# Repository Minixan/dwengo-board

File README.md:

After nearly a year of development, lots of new features and thousands of other improvements, Django 1.1 is here and ready for prime time!

For a full rundown of what's new and what's changed, consult the release notes; to grab a copy, swing by the Django download page. And for the security-conscious, signed checksums for the release tarball are available.

This release also contains the security update rolled out earlier tonight for older release series.

Django 1.1 is the result of hard work by hundreds of people who've contributed code to Django and many more who've donated their time to reporting, triaging, tracking down and helping to fix bugs and develop new features. Django literally would not be able to happen without all of you, so stop and give yourselves (and any other contributors you know) a pat on the back.

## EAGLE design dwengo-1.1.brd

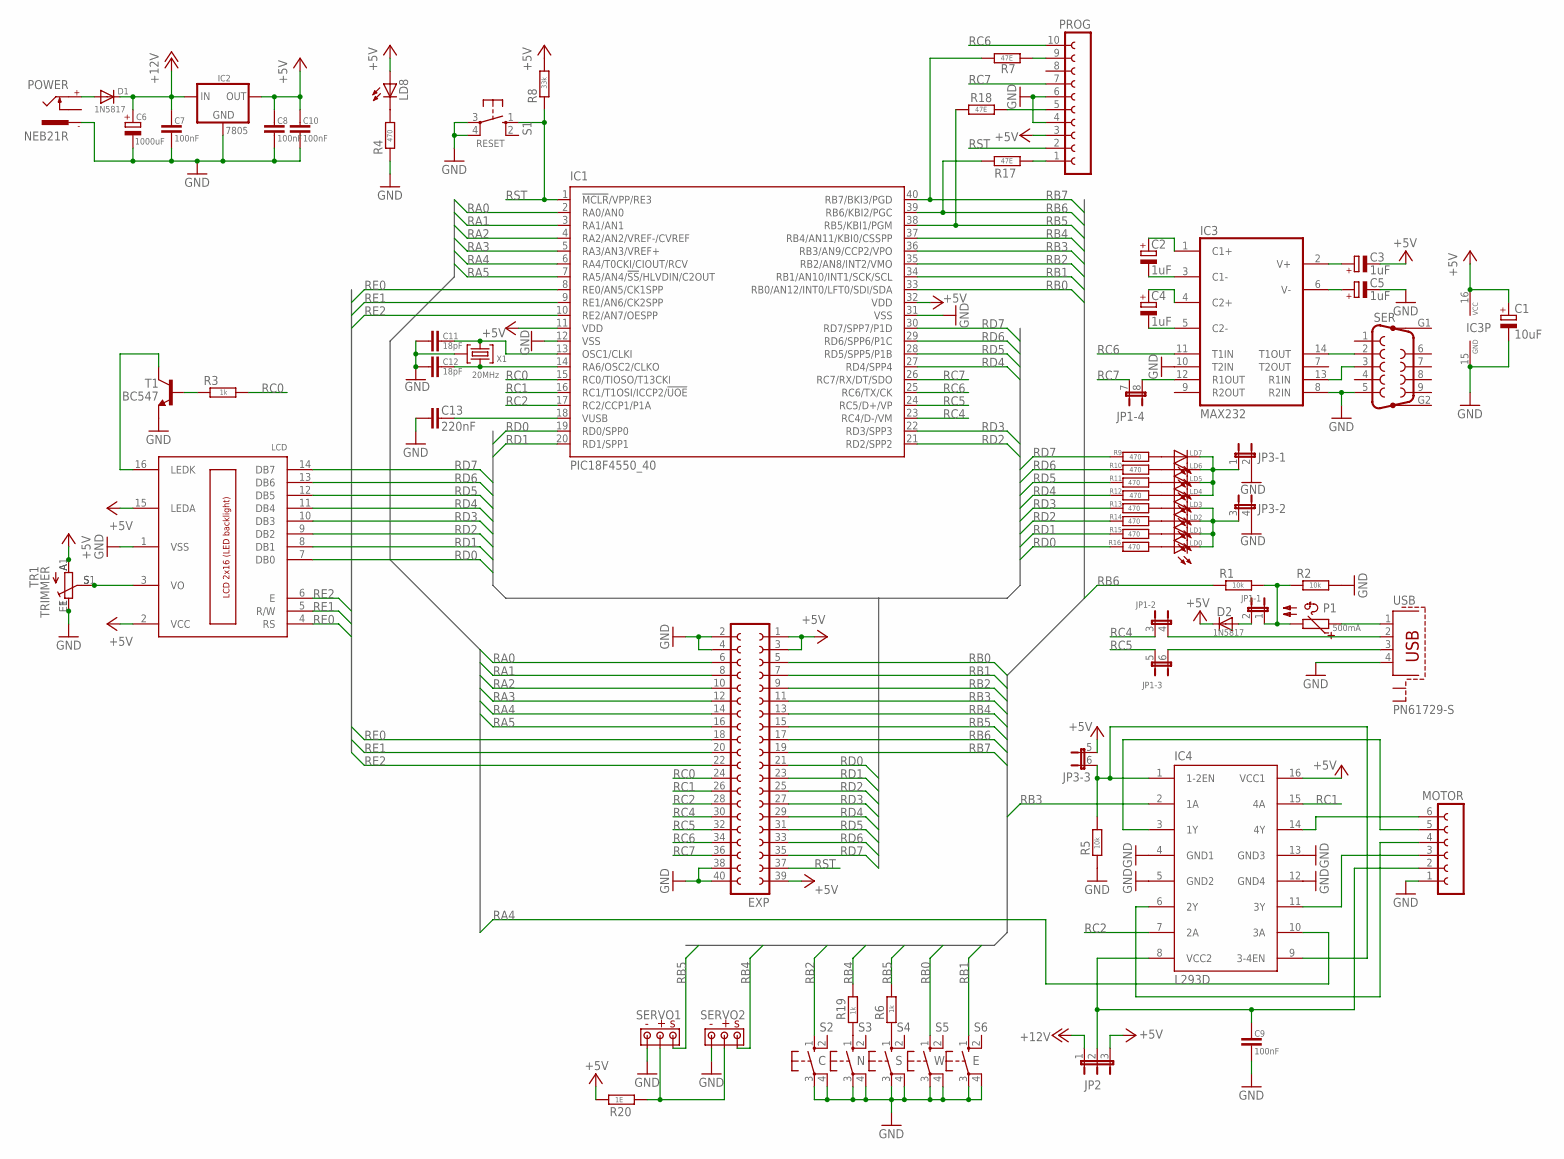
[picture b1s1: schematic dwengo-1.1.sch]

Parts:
C1: 10uF; E2-5
C2, C3, C4, C5: 1uF; E2-5
C6: 1000uF; E5-10,5
C7, C8, C9, C10: 100nF; C-EU050-025X075
C11, C12: 18pF; C-EU050-024X044
C13: 220nF; C-EU050-035X075
D1, D2: 1N5817; DO41-10
EXP: FE20-2W
IC1: PIC18F4550_40; DIL40
IC2: 7805; 78XXS
IC3: MAX232; DIL16
IC4: L293D; DIL16
JP1: JP2_4
JP2: JP_3MOTOR; JP_MOTOR
JP3: JP3QE; JP3Q
LCD: LCD_2X16; HY-1602F
LD0, LD1, LD2, LD3, LD4, LD5, LD6, LD7, LD8: LED3MM
MOTOR: MOTOR
P1: 500mA; POLYSWITCH
POWER: NEB21R
PROG: PROG_CONNECTOR
R1, R2, R5: 10k; 0204/7
R3, R6, R19: 1k; 0204/7
R4, R9, R10, R11, R12, R13, R14, R15, R16: 470; 0204/7
R7, R17, R18: 47E; 0204/7
R8: 33k; 0204/7
R20: 1E; 0204/7
S1, S2, S3, S4, S5, S6: 10-XX; B3F-10XX
SER: F09HP
SERVO1, SERVO2: SERVO
T1: BC547; TO92
TR1: TRIMMER
USB: PN61729-S
X1: 20MHz; CRYSTAL_RES

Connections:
+5V: C1.+, C3.-, C8.2, C10.2, D2.C, EXP.1, EXP.3, EXP.39, IC1.11 (VDD), IC1.32 (VDD), IC2.OUT, IC3.16 (VCC), IC4.16 (VCC1), JP2.3, JP3.5 (1), LCD.2 (VCC), LCD.15 (LEDA), LD8.A, PROG.3, R8.2, R20.1, TR1.A, TR1.A1
+12V: C6.+, C7.2, D1.C, IC2.IN, JP2.1
GND: C1.-, C5.-, C6.-, C7.1, C8.1, C9.1, C10.1, C11.2, C12.2, C13.2, EXP.2, EXP.4, EXP.38, EXP.40, IC1.12 (VSS), IC1.31 (VSS), IC2.GND, IC3.8 (R2IN), IC3.10 (T2IN), IC3.15 (GND), IC4.4 (GND1), IC4.5 (GND2), IC4.12 (GND4), IC4.13 (GND3), JP3.2, JP3.4 (2), LCD.1 (VSS), MOTOR.1, POWER.-, PROG.4, PROG.6, R2.2, R4.1, R5.1, S1.3, S1.4 (P1), S2.3, S2.4 (P1), S3.3, S3.4 (P1), S4.3, S4.4 (P1), S5.3, S5.4 (P1), S6.3, S6.4 (P1), SER.5, SERVO1.-, SERVO2.-, T1.1 (E), TR1.E, TR1.E1, USB.4, X1.P$1 (3)
unnamed: C9.2, IC4.8 (VCC2), JP2.2, MOTOR.2
unnamed: C11.1, IC1.13 (OSC1/CLKI), X1.2
unnamed: C12.1, IC1.14 (RA6/OSC2/CLKO), X1.1
unnamed: C2.+, IC3.1 (C1+)
unnamed: C2.-, IC3.3 (C1-)
unnamed: C4.+, IC3.4 (C2+)
unnamed: C4.-, IC3.5 (C2-)
unnamed: IC3.13 (R1IN), SER.3
unnamed: LCD.3 (VO), TR1.S, TR1.S1
unnamed: LD7.A, R9.2
unnamed: LD6.A, R10.2
unnamed: LD5.A, R11.2
unnamed: LD4.A, R12.2
unnamed: LD3.A, R13.2
unnamed: LD2.A, R14.2
unnamed: LD1.A, R15.2
unnamed: LD0.A, R16.2
unnamed: JP3.1, LD4.K (C), LD5.K (C), LD6.K (C), LD7.K (C)
unnamed: JP3.3 (1), LD0.K (C), LD1.K (C), LD2.K (C), LD3.K (C)
unnamed: C13.1, IC1.18 (VUSB)
unnamed: C3.+, IC3.2 (V+)
unnamed: C5.+, IC3.6 (V-)
unnamed: IC3.14 (T1OUT), SER.2
unnamed: LCD.16 (LEDK), T1.3 (C)
unnamed: LD8.K (C), R4.2
unnamed: IC3.12 (R1OUT), JP1.8 (2)
unnamed: JP1.6 (2), USB.3
unnamed: R3.1, T1.2 (B)
unnamed: P1.1, USB.1
unnamed: D2.A, JP1.2
unnamed: D1.A, POWER.+
unnamed: IC4.14 (4Y), MOTOR.6
unnamed: IC4.11 (3Y), MOTOR.3
unnamed: IC4.1 (1-2EN), IC4.9 (3-4EN), JP3.6 (2), R5.2
unnamed: IC4.6 (2Y), MOTOR.4
unnamed: IC4.3 (1Y), MOTOR.5
unnamed: JP1.4 (2), USB.2
unnamed: PROG.9, R7.2
unnamed: PROG.1, R17.2
unnamed: PROG.5, R18.2
unnamed: JP1.1, P1.2, R1.1, R2.1
unnamed: R19.1, S3.1 (S)
unnamed: R6.1, S4.1 (S)
unnamed: R20.2, SERVO1.+, SERVO2.+
RA0: EXP.6, IC1.2 (RA0/AN0)
RA1: EXP.8, IC1.3 (RA1/AN1)
RA2: EXP.10, IC1.4 (RA2/AN2/VREF-/CVREF)
RA3: EXP.12, IC1.5 (RA3/AN3/VREF+)
RA4: EXP.14, IC1.6 (RA4/T0CKI/CIOUT/RCV), IC4.10 (3A)
RA5: EXP.16, IC1.7 (RA5/AN4/!SS!/HLVDIN/C2OUT)
RB0: EXP.5, IC1.33 (RB0/AN12/INT0/LFT0/SDI/SDA), S5.1 (S)
RB1: EXP.7, IC1.34 (RB1/AN10/INT1/SCK/SCL), S6.1 (S)
RB2: EXP.9, IC1.35 (RB2/AN8/INT2/VMO), S2.1 (S)
RB3: EXP.11, IC1.36 (RB3/AN9/CCP2/VPO), IC4.2 (1A)
RB4: EXP.13, IC1.37 (RB4/AN11/KBI0/CSSPP), R19.2, SERVO2.S
RB5: EXP.15, IC1.38 (RB5/KBI1/PGM), R6.2, R18.1, SERVO1.S
RB6: EXP.17, IC1.39 (RB6/KBI2/PGC), R1.2, R17.1
RB7: EXP.19, IC1.40 (RB7/BKI3/PGD), R7.1
RC0: EXP.24, IC1.15 (RC0/TIOSO/T13CKI), R3.2
RC1: EXP.26, IC1.16 (RC1/T1OSI/ICCP2/!UOE), IC4.15 (4A)
RC2: EXP.28, IC1.17 (RC2/CCP1/P1A), IC4.7 (2A)
RC4: EXP.30, IC1.23 (RC4/D-/VM), JP1.3 (1)
RC5: EXP.32, IC1.24 (RC5/D+/VP), JP1.5 (1)
RC6: EXP.34, IC1.25 (RC6/TX/CK), IC3.11 (T1IN), PROG.10
RC7: EXP.36, IC1.26 (RC7/RX/DT/SDO), JP1.7 (1), PROG.7
RD0: EXP.21, IC1.19 (RD0/SPP0), LCD.7 (DB0), R16.1
RD1: EXP.23, IC1.20 (RD1/SPP1), LCD.8 (DB1), R15.1
RD2: EXP.25, IC1.21 (RD2/SPP2), LCD.9 (DB2), R14.1
RD3: EXP.27, IC1.22 (RD3/SPP3), LCD.10 (DB3), R13.1
RD4: EXP.29, IC1.27 (RD4/SPP4), LCD.11 (DB4), R12.1
RD5: EXP.31, IC1.28 (RD5/SPP5/P1B), LCD.12 (DB5), R11.1
RD6: EXP.33, IC1.29 (RD6/SPP6/P1C), LCD.13 (DB6), R10.1
RD7: EXP.35, IC1.30 (RD7/SPP7/P1D), LCD.14 (DB7), R9.1
RE0: EXP.18, IC1.8 (RE0/AN5/CK1SPP), LCD.4 (RS)
RE1: EXP.20, IC1.9 (RE1/AN6/CK2SPP), LCD.5 (R/W)
RE2: EXP.22, IC1.10 (RE2/AN7/OESPP), LCD.6 (E)
RST: EXP.37, IC1.1 (!MCLR!/VPP/RE3), PROG.2, R8.1, S1.1 (S)

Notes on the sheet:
RESET

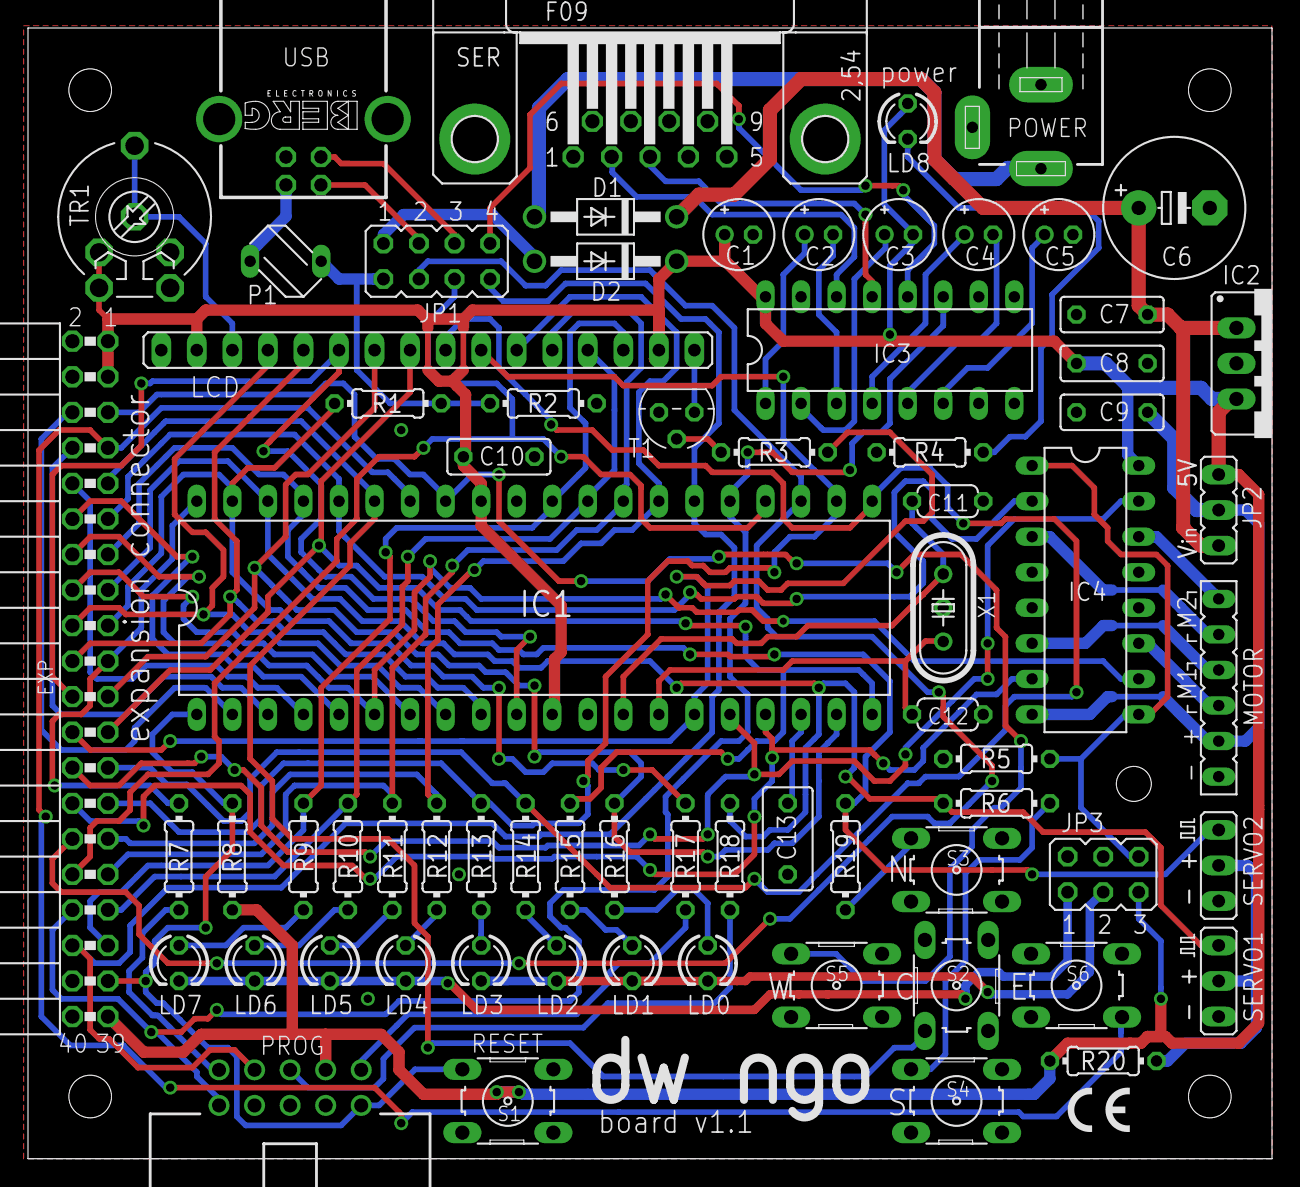
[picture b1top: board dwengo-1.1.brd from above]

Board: 2 copper layers, 88.9 x 80.8 mm, 72 parts (0 on the bottom side), 80 nets.

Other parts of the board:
U$1: LOGO_ML
U$4: CE_MED

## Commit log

2018-01-24 second commit
